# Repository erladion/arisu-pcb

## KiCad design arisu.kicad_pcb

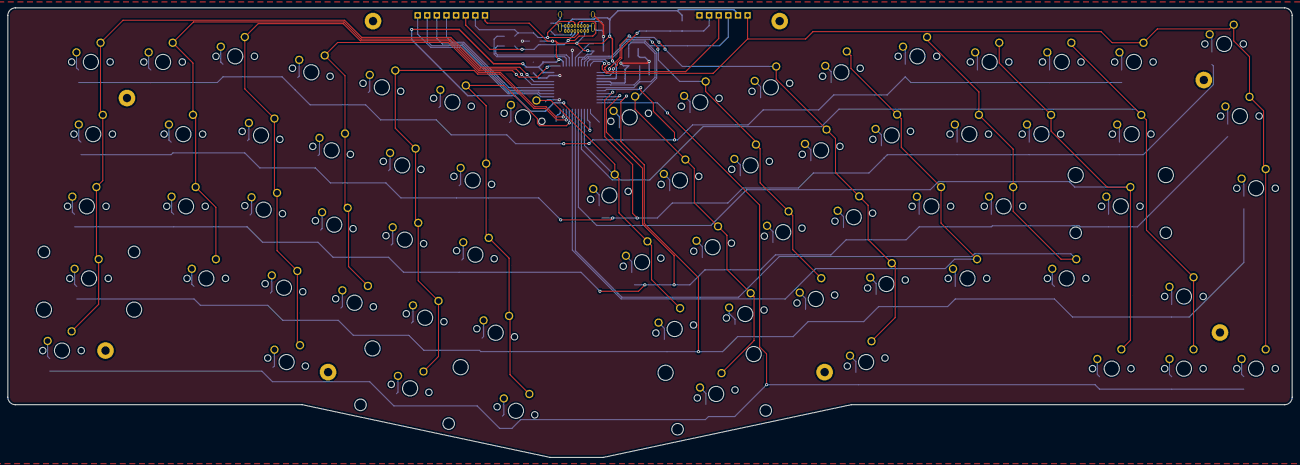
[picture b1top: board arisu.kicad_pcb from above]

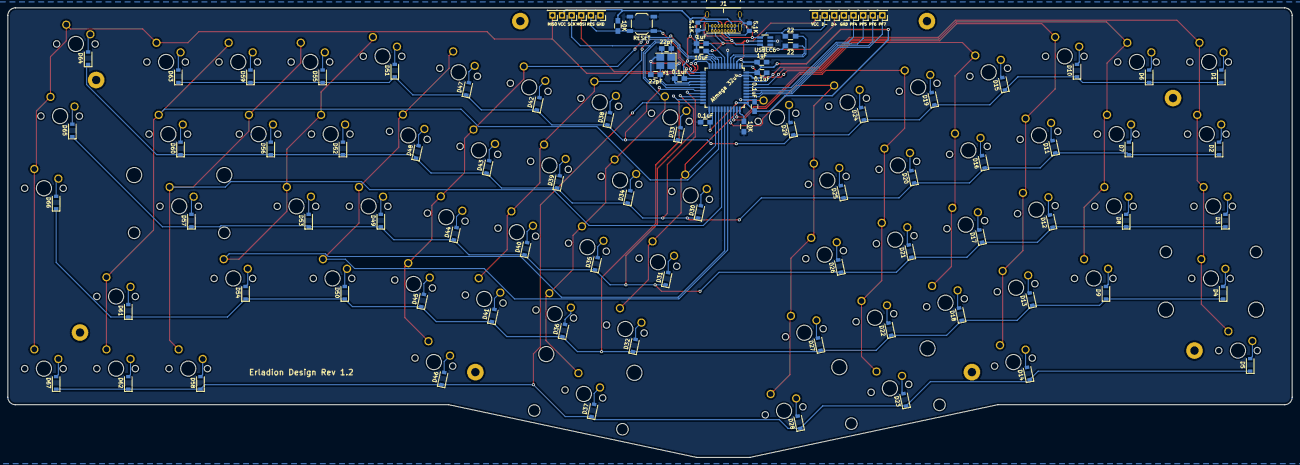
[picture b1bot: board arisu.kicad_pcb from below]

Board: 2 copper layers, 339.1 x 118.7 mm, 176 parts (101 on the bottom side), 105 nets.

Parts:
0.1uF, 0.1uF#2, 0.1uF#3, 0.1uF#4: 0.1uF; C_0805_HandSoldering
1uF: 1uF (±10%); C_0805_HandSoldering
1uF#2: 1uF; C_0805_HandSoldering
5.1K, 5.1K#2: 5.1K; R_0805_2012Metric_Pad1.15x1.40mm_HandSolder
10K, 10K#2: 10K; R_0805_HandSoldering
10uF: 10uF; C_0805_HandSoldering
22, 22#2: 22; R_0805_HandSoldering
22pF, 22pF#2: 22pF; C_0805_HandSoldering
Atmega 32u4: ATmega32U4-AU; TQFP-44_10x10mm_Pitch0.8mm
D1, D2, D3, D4, D5, D6, D7, D8, D9, D10, D11, D12, D13, D14, D15, D16, D17, D18, D19, D20, D21, D22, D23, D24, D25, D26, D27, D28, D29, D30, D31, D32, D33, D34, D35, D36, D37, D38, D39, D40, D41, D42, D43, D44, D45, D46, D47, D48, D49, D50, D51, D52, D53, D54, D55, D56, D57, D58, D59, D60, D61, D62, D63, D64, D65, D66, D67: D; D_SOD-123
D+: D+; Pin_Header_Straight_1x01_Pitch2.54mm
D-: D-; Pin_Header_Straight_1x01_Pitch2.54mm
GND: GND; Pin_Header_Straight_1x01_Pitch2.54mm
GND#2: GND; Pin_Header_Straight_1x01_Pitch2.54mm
H1, H2, H3, H4, H5, H6, H7, H8: MountingHole; MountingHole_2.2mm_M2_Pad
J1: USB_C_Receptacle_USB2.0; USB_C_GCT_USB4085
MISO: MISO; Pin_Header_Straight_1x01_Pitch2.54mm
MOSI: MOSI; Pin_Header_Straight_1x01_Pitch2.54mm
PF4: PF4; Pin_Header_Straight_1x01_Pitch2.54mm
PF5: PF5; Pin_Header_Straight_1x01_Pitch2.54mm
PF6: PF6; Pin_Header_Straight_1x01_Pitch2.54mm
PF7: PF7; Pin_Header_Straight_1x01_Pitch2.54mm
RES: RES; Pin_Header_Straight_1x01_Pitch2.54mm
RESET: SW_Push; SW_SPST_TL3342
SCK: SCK; Pin_Header_Straight_1x01_Pitch2.54mm
SW1, SW6, SW7, SW8, SW9, SW10, SW11, SW12, SW13, SW15, SW16, SW17, SW18, SW19, SW20, SW21, SW22, SW24, SW25, SW26, SW27, SW28, SW29, SW30, SW31, SW32, SW33, SW34, SW35, SW36, SW38, SW39, SW40, SW41, SW42, SW43, SW44, SW45, SW47, SW48, SW49, SW50, SW51, SW52, SW53, SW55, SW56, SW58, SW59, SW61, SW62, SW63, SW64, SW65, SW66, SW67: SW_Push; SW_Cherry_MX_1.00u_PCB
SW2, SW5, SW14, SW46, SW60: SW_Push; SW_Cherry_MX_1.50u_PCB
SW3, SW54: SW_Push; SW_Cherry_MX_1.75u_PCB
SW4: SW_Push; SW_Cherry_MX_2.25u_PCB
SW23: SW_Push; SW_Cherry_MX_2.00u_PCB_ReversedStabilizers
SW37: SW_Push; SW_Cherry_MX_2.75u_PCB_ReversedStabilizers
SW57: SW_Push; SW_Cherry_MX_2.25u_PCB_ReversedStabilizers
USBLC6: USBLC6-2SC6; SOT-23-6_Handsoldering
VCC: VCC; Pin_Header_Straight_1x01_Pitch2.54mm
VCC#2: VCC; Pin_Header_Straight_1x01_Pitch2.54mm
Y1: Crystal_GND24; Crystal_SMD_SeikoEpson_FA238-4pin_3.2x2.5mm_HandSoldering

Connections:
/MISO: Atmega 32u4.11, MISO.1, SW63.1, SW64.1, SW65.1, SW66.1, SW67.1
/MOSI: Atmega 32u4.10, MOSI.1
/PF4: Atmega 32u4.39, PF4.1
/PF5: Atmega 32u4.38, PF5.1
/PF6: Atmega 32u4.37, PF6.1
/PF7: Atmega 32u4.36, PF7.1
/SCK: Atmega 32u4.9, SCK.1, SW33.1, SW34.1, SW35.1, SW36.1, SW37.1
/col0: Atmega 32u4.41, SW1.1, SW2.1, SW3.1, SW4.1, SW5.1
/col1: Atmega 32u4.40, SW6.1, SW7.1, SW8.1, SW9.1
/col2: Atmega 32u4.1, SW10.1, SW11.1, SW12.1, SW13.1, SW14.1
/col3: Atmega 32u4.32, SW15.1, SW16.1, SW17.1, SW18.1
/col4: Atmega 32u4.31, SW19.1, SW20.1, SW21.1, SW22.1, SW23.1
/col5: Atmega 32u4.30, SW24.1, SW25.1, SW26.1, SW27.1, SW28.1
/col6: Atmega 32u4.25, SW29.1, SW30.1, SW31.1, SW32.1
/col8: Atmega 32u4.8, SW38.1, SW39.1, SW40.1, SW41.1
/col9: Atmega 32u4.12, SW42.1, SW43.1, SW44.1, SW45.1, SW46.1
/col10: Atmega 32u4.29, SW47.1, SW48.1, SW49.1, SW50.1
/col11: Atmega 32u4.28, SW51.1, SW52.1, SW53.1, SW54.1
/col12: Atmega 32u4.27, SW55.1, SW56.1, SW57.1, SW58.1
/col13: Atmega 32u4.26, SW59.1, SW60.1, SW61.1, SW62.1
/row0: Atmega 32u4.18, D1.1, D6.1, D10.1, D15.1, D19.1, D24.1, D29.1, D33.1, D38.1, D42.1, D47.1, D51.1, D55.1, D59.1, D63.1
/row1: Atmega 32u4.19, D2.1, D7.1, D11.1, D16.1, D20.1, D25.1, D30.1, D34.1, D39.1, D43.1, D48.1, D52.1, D56.1, D60.1, D64.1
/row2: Atmega 32u4.20, D3.1, D8.1, D12.1, D17.1, D21.1, D26.1, D31.1, D35.1, D40.1, D44.1, D49.1, D53.1, D57.1, D65.1
/row3: Atmega 32u4.21, D4.1, D9.1, D13.1, D18.1, D22.1, D27.1, D32.1, D36.1, D41.1, D45.1, D50.1, D54.1, D61.1, D66.1
/row4: Atmega 32u4.22, D5.1, D14.1, D23.1, D28.1, D37.1, D46.1, D58.1, D62.1, D67.1
/~RES~: 10K.2, Atmega 32u4.13, RES.1, RESET.2
D+: 22#2.1, Atmega 32u4.4
D-: 22.1, Atmega 32u4.3
GND: 0.1uF.2, 0.1uF#2.2, 0.1uF#3.2, 0.1uF#4.2, 1uF.2, 1uF#2.2, 5.1K.1, 5.1K#2.1, 10K#2.2, 10uF.2, 22pF.1, 22pF#2.2, Atmega 32u4.5, Atmega 32u4.15, Atmega 32u4.23, Atmega 32u4.35, Atmega 32u4.43, GND.1, GND#2.1, J1.A1, J1.A12, J1.B1, J1.B12, J1.S1, RESET.1, USBLC6.2, Y1.2, Y1.4
unnamed: 1uF.1, Atmega 32u4.6
unnamed: D1.2, SW1.2
unnamed: D2.2, SW2.2
unnamed: D3.2, SW3.2
unnamed: D4.2, SW4.2
unnamed: D5.2, SW5.2
unnamed: D6.2, SW6.2
unnamed: D7.2, SW7.2
unnamed: D8.2, SW8.2
unnamed: D9.2, SW9.2
unnamed: D10.2, SW10.2
unnamed: D11.2, SW11.2
unnamed: D12.2, SW12.2
unnamed: D13.2, SW13.2
unnamed: D14.2, SW14.2
unnamed: D15.2, SW15.2
unnamed: D16.2, SW16.2
unnamed: D17.2, SW17.2
unnamed: D18.2, SW18.2
unnamed: D19.2, SW19.2
unnamed: D20.2, SW20.2
unnamed: D21.2, SW21.2
unnamed: D22.2, SW22.2
unnamed: D23.2, SW23.2
unnamed: D24.2, SW24.2
unnamed: D25.2, SW25.2
unnamed: D26.2, SW26.2
unnamed: D27.2, SW27.2
unnamed: D28.2, SW28.2
unnamed: D29.2, SW29.2
unnamed: D30.2, SW30.2
unnamed: D31.2, SW31.2
unnamed: D32.2, SW32.2
unnamed: D33.2, SW33.2
unnamed: D34.2, SW34.2
unnamed: D35.2, SW35.2
unnamed: D36.2, SW36.2
unnamed: D37.2, SW37.2
unnamed: D38.2, SW38.2
unnamed: D39.2, SW39.2
unnamed: D40.2, SW40.2
unnamed: D41.2, SW41.2
unnamed: D42.2, SW42.2
unnamed: D43.2, SW43.2
unnamed: D44.2, SW44.2
unnamed: D45.2, SW45.2
unnamed: D46.2, SW46.2
unnamed: D47.2, SW47.2
unnamed: D48.2, SW48.2
unnamed: D49.2, SW49.2
unnamed: D50.2, SW50.2
unnamed: D51.2, SW51.2
unnamed: D52.2, SW52.2
unnamed: D53.2, SW53.2
unnamed: D54.2, SW54.2
unnamed: D55.2, SW55.2
unnamed: D56.2, SW56.2
unnamed: D57.2, SW57.2
unnamed: D58.2, SW58.2
unnamed: D59.2, SW59.2
unnamed: D60.2, SW60.2
unnamed: D61.2, SW61.2
unnamed: D62.2, SW62.2
unnamed: D63.2, SW63.2
unnamed: D64.2, SW64.2
unnamed: D65.2, SW65.2
unnamed: D66.2, SW66.2
unnamed: D67.2, SW67.2
unnamed: 5.1K#2.2, J1.A5
unnamed: 22#2.2, D+.1, J1.A6, J1.B6, USBLC6.6
unnamed: 22.2, D-.1, J1.A7, J1.B7, USBLC6.4
unnamed: 5.1K.2, J1.B5
unnamed: 10K#2.1, Atmega 32u4.33
VCC: 0.1uF.1, 0.1uF#2.1, 0.1uF#3.1, 0.1uF#4.1, 1uF#2.1, 10K.1, 10uF.1, Atmega 32u4.2, Atmega 32u4.7, Atmega 32u4.14, Atmega 32u4.24, Atmega 32u4.34, Atmega 32u4.44, J1.A4, J1.A9, J1.B4, J1.B9, USBLC6.5, VCC.1, VCC#2.1
XTAL1: 22pF.2, Atmega 32u4.17, Y1.1
XTAL2: 22pF#2.1, Atmega 32u4.16, Y1.3

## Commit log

2020-09-14 USB-C version of the arisu
2020-09-14 First commit with arisu using a stm32f411 and usb-c
2020-09-15 Hide references for switches on the pcb
2020-09-16 Update references to show values
